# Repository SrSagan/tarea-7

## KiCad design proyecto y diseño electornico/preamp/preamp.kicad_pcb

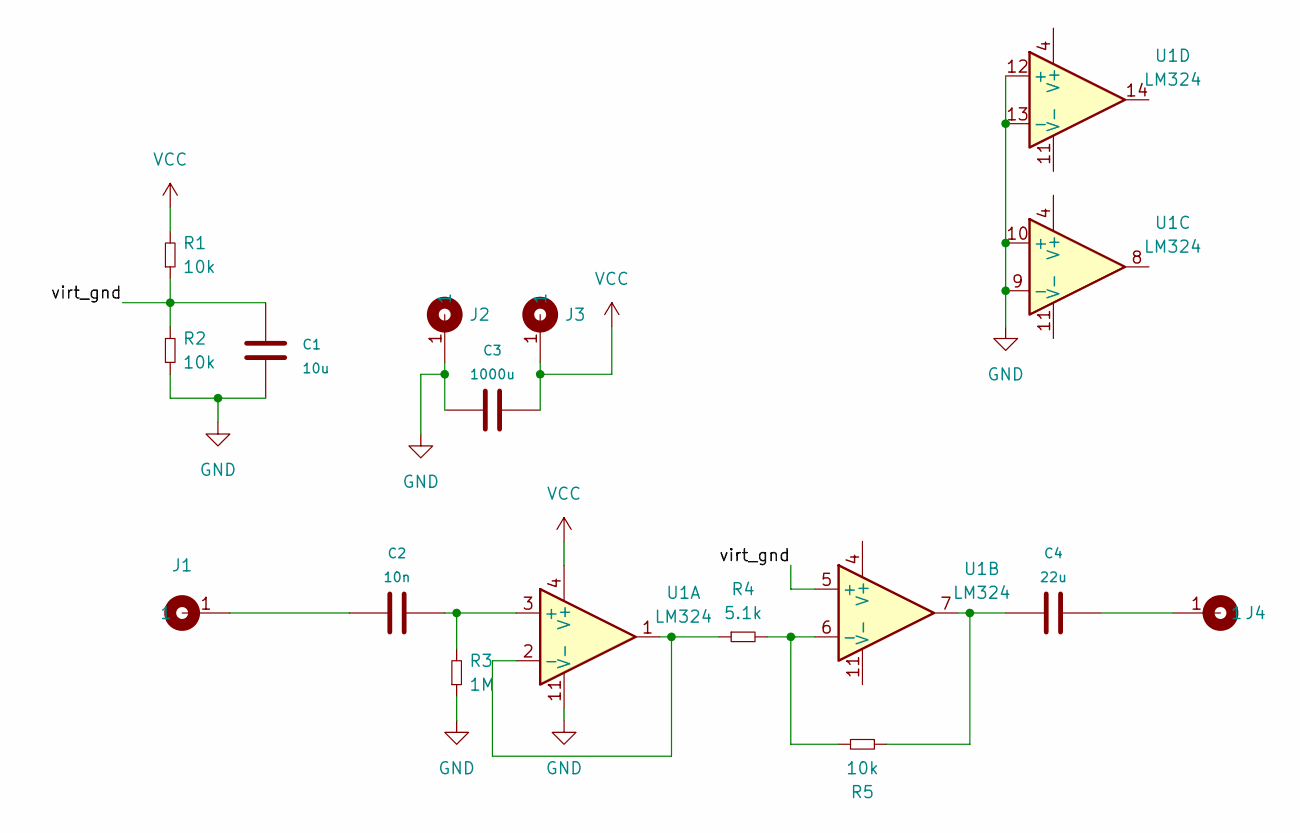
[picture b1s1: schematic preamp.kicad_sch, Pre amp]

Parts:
C1: 10u; CAP_0.2
C2: 10n; CAP_0.2
C3: 1000u; CAP_ELEC_10X8mm
C4: 22u; CAP_ELEC_5x11mm
J1, J2, J3, J4: Cable_PAD; Cable_Doble_1,5mm
R1, R2, R5: 10k; RES0.3
R3: 1M; RES0.3
R4: 5.1k; RES0.3
U1: LM324; DIP-14

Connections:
/virt_gnd: C1.1, R1.1, R2.2, U1.5 (+)
GND: C1.2, C3.1, J2.1, R2.1, R3.1, U1.9 (-), U1.10 (+), U1.11 (V-), U1.12 (+), U1.13 (-)
unnamed: C2.1, R3.2, U1.3 (+)
unnamed: C2.2, J1.1
unnamed: C4.1, R5.2, U1.7
unnamed: C4.2, J4.1
unnamed: R4.1, U1.1, U1.2 (-)
unnamed: R4.2, R5.1, U1.6 (-)
VCC: C3.2, J3.1, R1.2, U1.4 (V+)

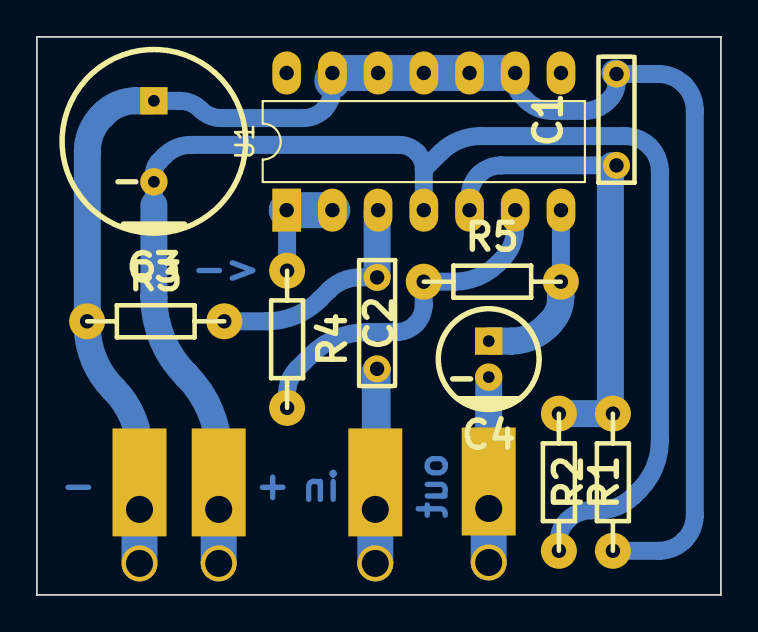
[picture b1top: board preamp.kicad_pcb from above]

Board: 2 copper layers, 38.0 x 31.0 mm, 14 parts (0 on the bottom side), 9 nets.

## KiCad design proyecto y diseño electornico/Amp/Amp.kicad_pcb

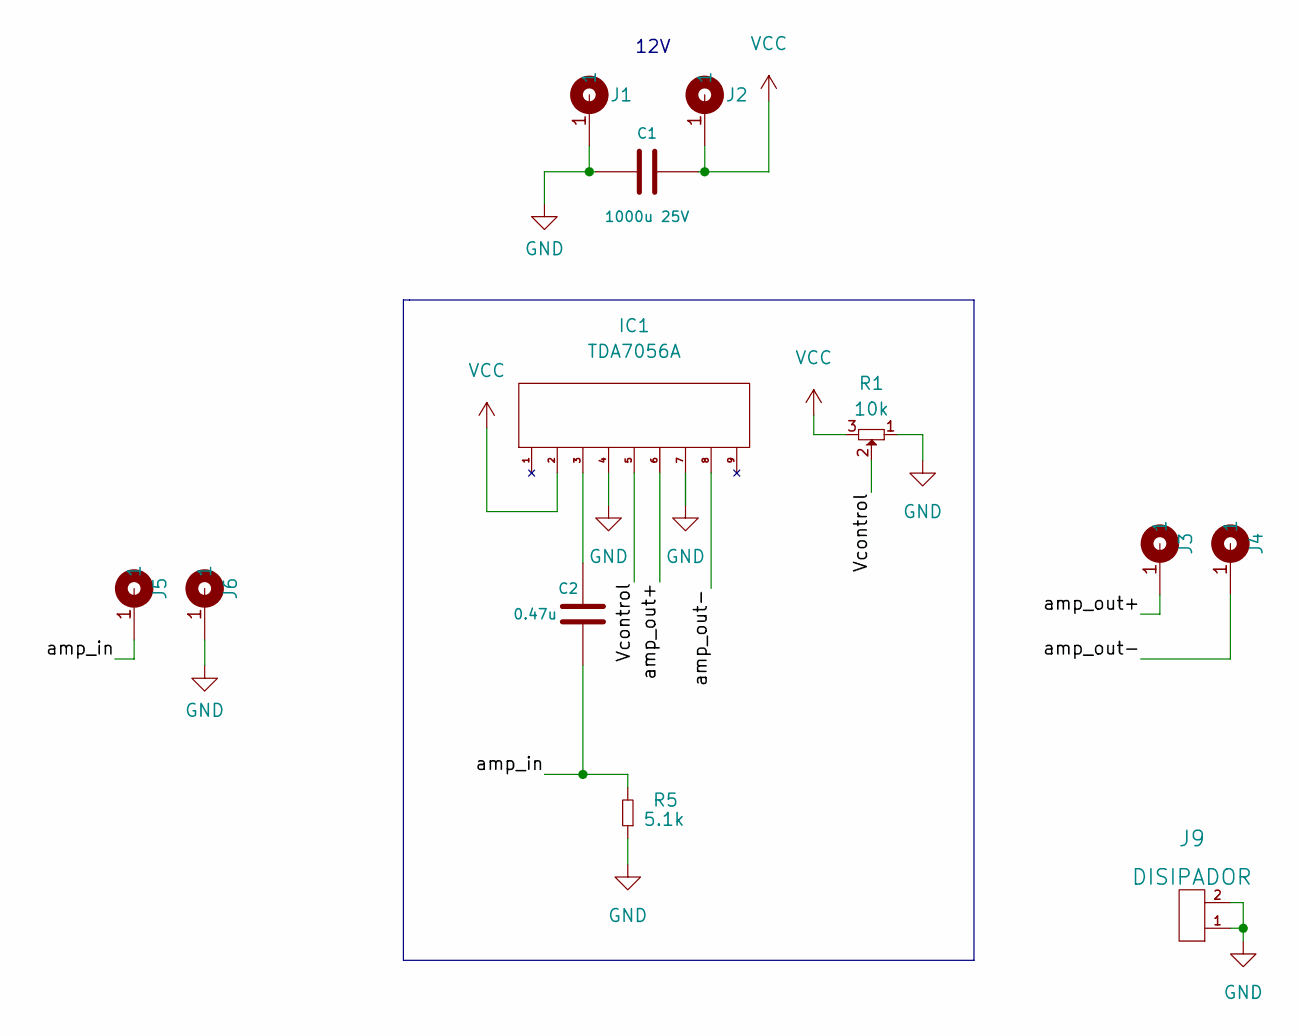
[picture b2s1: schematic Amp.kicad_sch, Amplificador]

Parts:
C1: 1000u 25V; CAP_ELEC_8x11.5mm
C2: 0.47u; CAP_ELEC_5x11mm
IC1: TDA7056A; SOT-110
J1, J2, J3, J4, J5, J6: Cable_PAD; Cable_Doble_1,5mm
J9: DISIPADOR; Disipador_SOT110-1
R1: 10k; Potenciometro
R5: 5.1k; RES0.3

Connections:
/Vcontrol: IC1.5 (VC), R1.2
/amp_in: C2.2, J5.1, R5.2
/amp_out+: IC1.6 (OUT+), J3.1
/amp_out-: IC1.8 (OUT-), J4.1
GND: C1.2, IC1.4 (GND1), IC1.7 (GND2), J1.1, J6.1, J9.1, J9.2, R1.1, R5.1
unnamed: C2.1, IC1.3 (Vin)
VCC: C1.1, IC1.2 (Vcc), J2.1, R1.3

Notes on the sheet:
12V

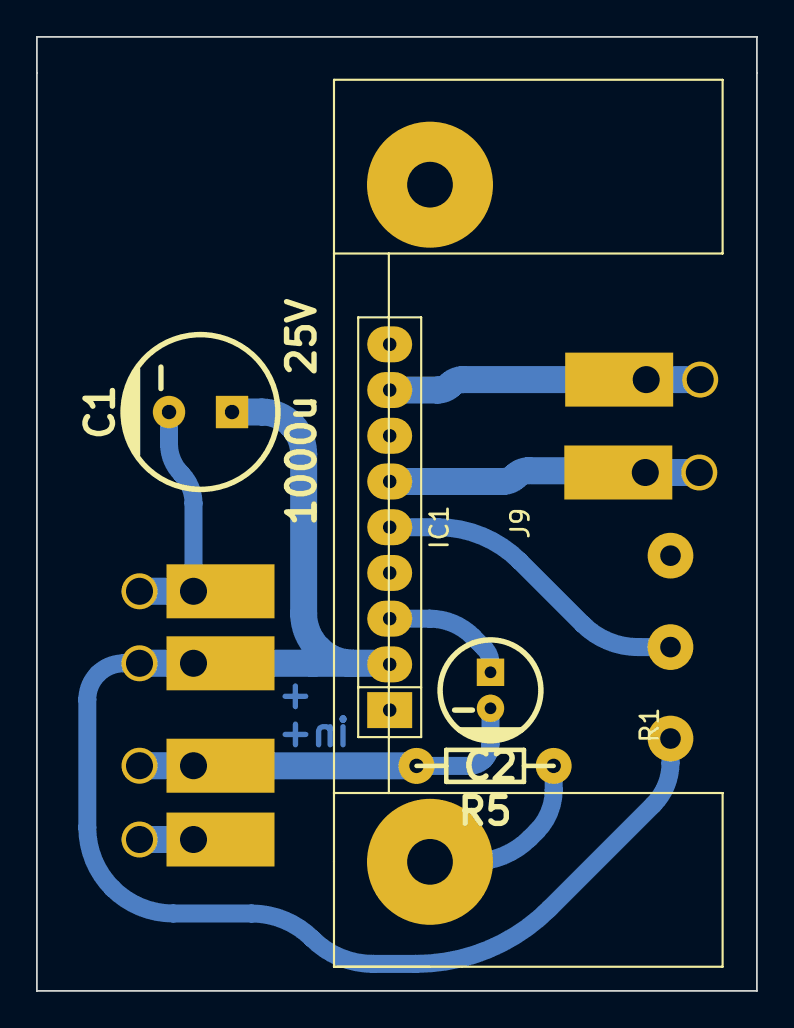
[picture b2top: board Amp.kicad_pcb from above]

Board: 2 copper layers, 40.0 x 53.0 mm, 12 parts (0 on the bottom side), 7 nets.

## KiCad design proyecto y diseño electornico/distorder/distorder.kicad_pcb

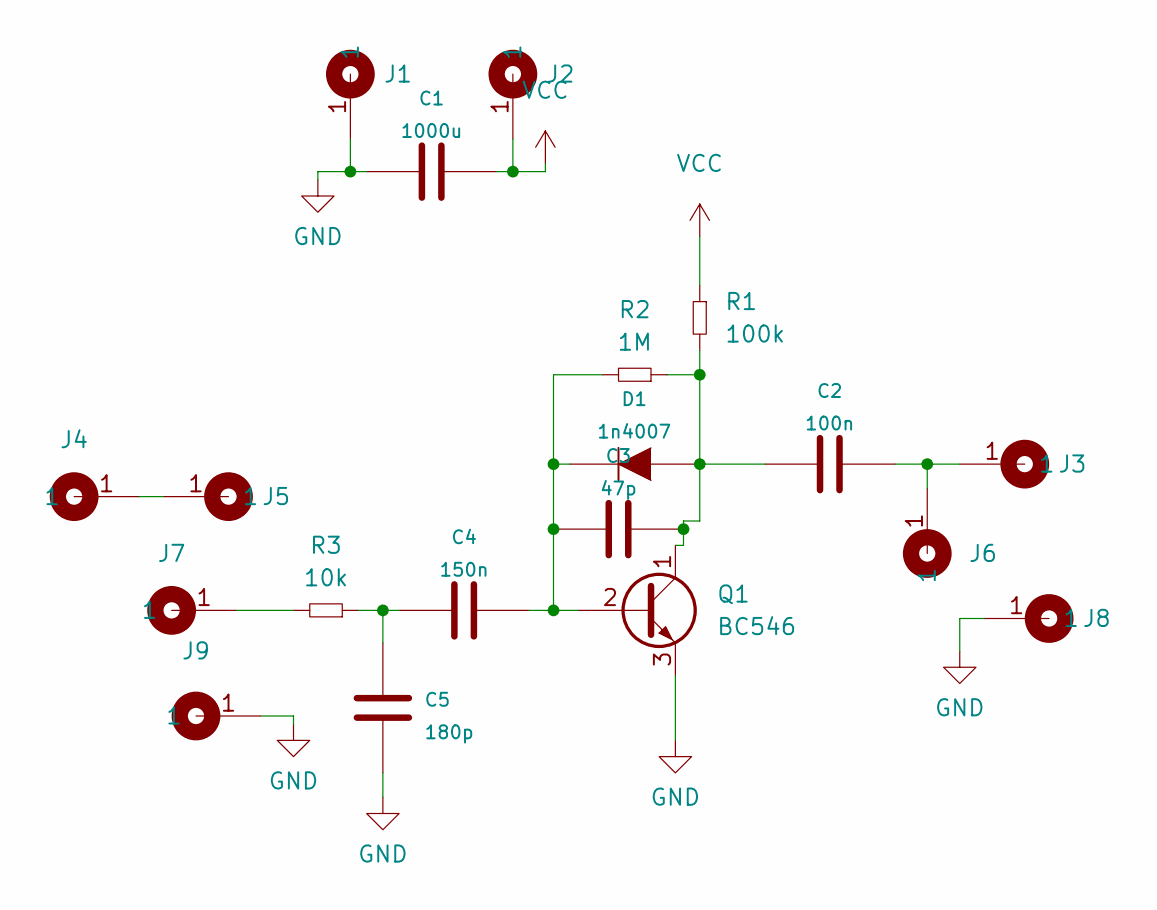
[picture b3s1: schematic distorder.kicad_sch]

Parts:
C1: 1000u; CAP_ELEC_8x11.5mm
C2: 100n; CAP_0.1
C3: 47p; CAP_0.1
C4: 150n; CAP_0.1
C5: 180p; CAP_0.1
D1: 1n4007; DO-41
J1: pw-; Cable_Doble_1,5mm
J2: pw+; Cable_Doble_1,5mm
J3: Out+; Cable_Doble_1,5mm
J4: In+; Cable_Doble_1,5mm
J5: Switch Mid; Cable_Doble_1,5mm
J6, J7: Switch; Cable_Doble_1,5mm
J8: Out-; Cable_Doble_1,5mm
J9: In-; Cable_Doble_1,5mm
Q1: BC546; to92
R1: 100k; RES0.2
R2: 1M; RES0.2
R3: 10k; RES0.2

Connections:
GND: C1.1, C5.1, J1.1, J8.1, J9.1, Q1.3 (E)
unnamed: C2.1, C3.2, D1.1 (A), Q1.1 (C), R1.2, R2.1
unnamed: C2.2, J3.1, J6.1
unnamed: C3.1, C4.2, D1.2 (K), Q1.2 (B), R2.2
unnamed: C4.1, C5.2, R3.1
unnamed: J4.1, J5.1
unnamed: J7.1, R3.2
VCC: C1.2, J2.1, R1.1

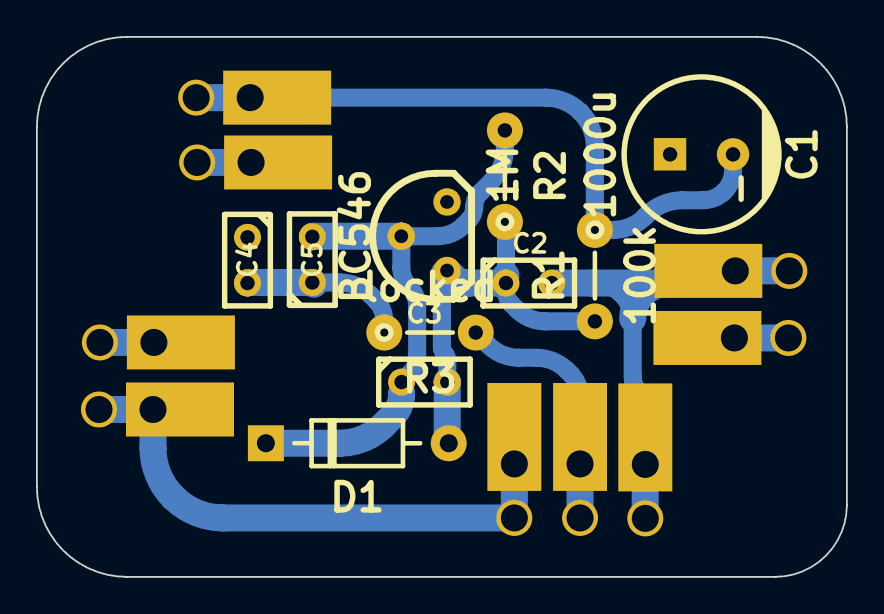
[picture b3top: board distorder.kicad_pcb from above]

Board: 2 copper layers, 45.0 x 30.0 mm, 19 parts (0 on the bottom side), 8 nets.

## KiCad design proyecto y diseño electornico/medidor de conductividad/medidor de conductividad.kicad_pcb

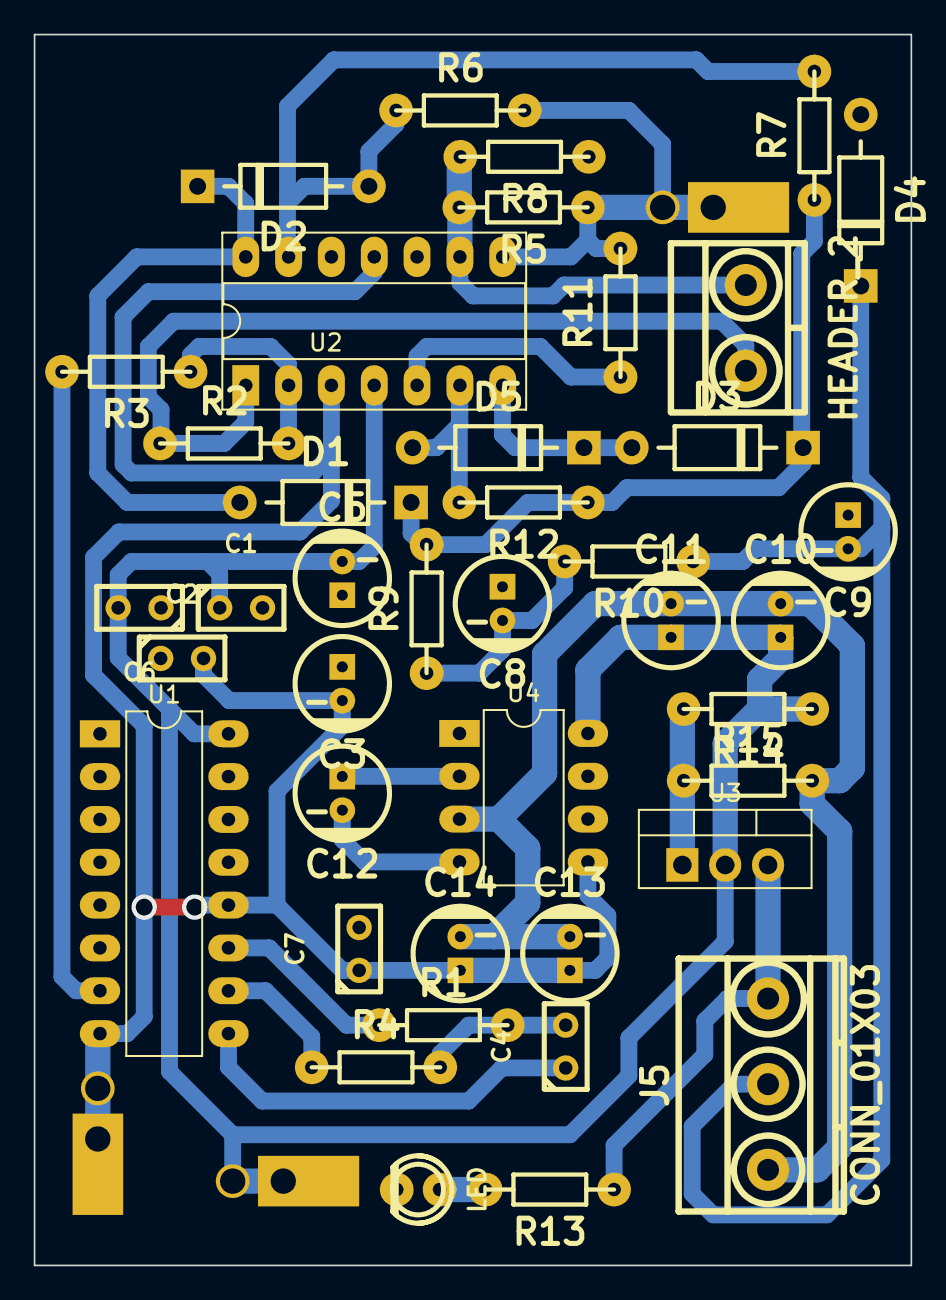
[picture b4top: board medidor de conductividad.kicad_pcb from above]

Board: 2 copper layers, 52.0 x 73.0 mm, 44 parts (0 on the bottom side), 25 nets.

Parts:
C1, C2, C6, C7: 100n; CAP_0.1
C3, C5: 4.7u; CAP_ELEC_5x11mm
C4: 1n; CAP_0.1
C8, C9: 1u; CAP_ELEC_5x11mm
C10, C12, C13: 10u; CAP_ELEC_5x11mm
C11, C14: 100u; CAP_ELEC_5x11mm
D1, D2, D3, D5: 1N4148; DO-41
D4: 1N5819W; DO-41
J1: HEADER_2; BORNERA2_AZUL
J2, J3, J4: Cable_PAD; Cable_Doble_1,5mm
J5: CONN_01X03; BORNERA3
LED1: LED; led_3mm_red
R1, R3: 100k; RES0.3
R2: 6.8k; RES0.3
R4, R6, R7, R9, R10, R11, R12: 10k; RES0.3
R5, R13: 5.6k; RES0.3
R8: 1M; RES0.3
R14: 3.3k; RES0.3
R15: 4.7k; RES0.3
U1: CD4060BM; DIP-16
U2: TL084; DIP-14
U3: LM317; TO-220-3_Vertical
U4: TC7660; DIP-8

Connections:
+3V0: C1.1, C5.2, C6.2, C10.1, C11.1, J3.1, R14.1, U1.16 (VDD), U2.4 (Vcc+), U3.2 (Vout), U4.8 (V+)
-3V3: C2.2, C3.2, C7.1, C13.1, C14.1, J4.1, U1.8 (VSS), U1.12 (Reset), U2.3 (+), U2.11 (Vcc-), U4.5 (Vout)
GND: C1.2, C2.1, C3.1, C5.1, C6.1, C7.2, C8.1, C9.1, C10.2, C11.2, C13.2, C14.2, D4.1 (A), J5.1, LED1.2 (K), R8.1, R15.2, U2.10 (+), U2.12 (+), U4.3 (GND)
unnamed: C4.1, U1.9 (ExtC)
unnamed: C4.2, R1.2, R4.2
unnamed: C8.2, R9.1, R10.2
unnamed: C9.2, D4.2 (K), J5.2, R10.1
unnamed: C12.1, U4.2 (Cap+)
unnamed: C12.2, U4.4 (Cap-)
unnamed: D1.1 (A), D2.2 (K), U2.14 (Out4)
unnamed: D1.2 (K), D3.2 (K), R7.1, R9.2, R12.1
unnamed: D2.1 (A), R6.1, R7.2, U2.13 (-)
unnamed: D3.1 (A), D5.2 (K), U2.7 (Out2)
unnamed: D5.1 (A), R12.2, U2.6 (-)
unnamed: J1.1, R2.1, U2.1 (Out1)
unnamed: J1.2, R5.2, R8.2, U2.9 (-)
unnamed: J2.1, R5.1, R6.2, R11.2, U2.8 (Out3)
unnamed: LED1.1 (A), R13.2
unnamed: R1.1, U1.11 (Clock)
unnamed: R2.2, R3.1, U2.2 (-)
unnamed: R3.2, U1.7 (Q4)
unnamed: R4.1, U1.10 (ExtR)
unnamed: R11.1, U2.5 (+)
unnamed: R14.2, R15.1, U3.1 (Adj)
VCC: J5.3, R13.1, U3.3 (Vin)

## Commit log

2022-03-03 commits
2022-03-03 horarios actualizados
2022-03-04 sistemas de control y instalaciones industriales
2022-03-08 electornica aplicada
2022-03-14 instalaciones industriales
2022-03-18 instalaciones ind
2022-03-25 ultima semana
2022-03-25 viernes
2022-04-13 Un monton de cosas
2022-04-22 22/4
2022-05-01 30/4
2022-05-04 test
2022-05-10 10/5
2022-05-14 14/7
2022-05-19 19/5
2022-06-15 14/6
2022-06-27 27/6
2022-09-21 27/9
2022-11-01 1/11
2022-12-02 2/12
